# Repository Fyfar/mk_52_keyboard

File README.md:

# MK-52 Keyboard PCB Replacement

This repository contains a custom PCB design intended to replace the original, non-repairable keyboard board of the Soviet calculator **Elektronika MK-52**.

The board was designed and routed in **KiCad** as a personal project to restore my own calculator. I decided to publish the design files in case they are useful to other MK-52 owners facing similar keyboard failures.

---

## Background

The original keyboard assembly of the Elektronika MK-52 is difficult or impossible to repair once the membrane or contact layers degrade. Since original spare parts are no longer available, creating a replacement PCB becomes a practical restoration approach.

This project provides:

- A reverse-engineered keyboard PCB layout
- A modern, manufacturable replacement board
- KiCad project files for modification or adaptation

---

## Project Status

This is a **hobbyist restoration project** created for personal use.  
It is not an officially supported product and is not affiliated with the original manufacturer.

The design was tested on my own calculator, but hardware variations, component tolerances, and assembly differences may affect compatibility.

---

## Repository Contents

- KiCad project files (`.kicad_pro`)
- Schematic files
- PCB layout files
- Production-ready Gerber files

---

## Tools Used

- KiCad (PCB design and routing)

---

## Disclaimer

This project is provided **as-is**, without any warranties of any kind.

- It is an amateur project.
- There is no guarantee that it will work in your specific device.
- Manufacturing and installing this PCB requires electronics experience.
- Any attempt to disassemble or repair your calculator may result in permanent damage.
- You assume full responsibility for any damage caused during repair or modification.

If you are not confident in your repair skills, consider consulting an experienced electronics technician.

---

## Why This Exists

The Elektronika MK-52 is an iconic programmable calculator, and many units are still functional except for keyboard failures. This project exists to help preserve and restore these devices instead of letting them become unusable due to a single non-repairable component.

---

## License

CERN Open Hardware Licence Version 2 - Permissive

---

If this project helped you restore your MK-52, feel free to share your results or improvements.

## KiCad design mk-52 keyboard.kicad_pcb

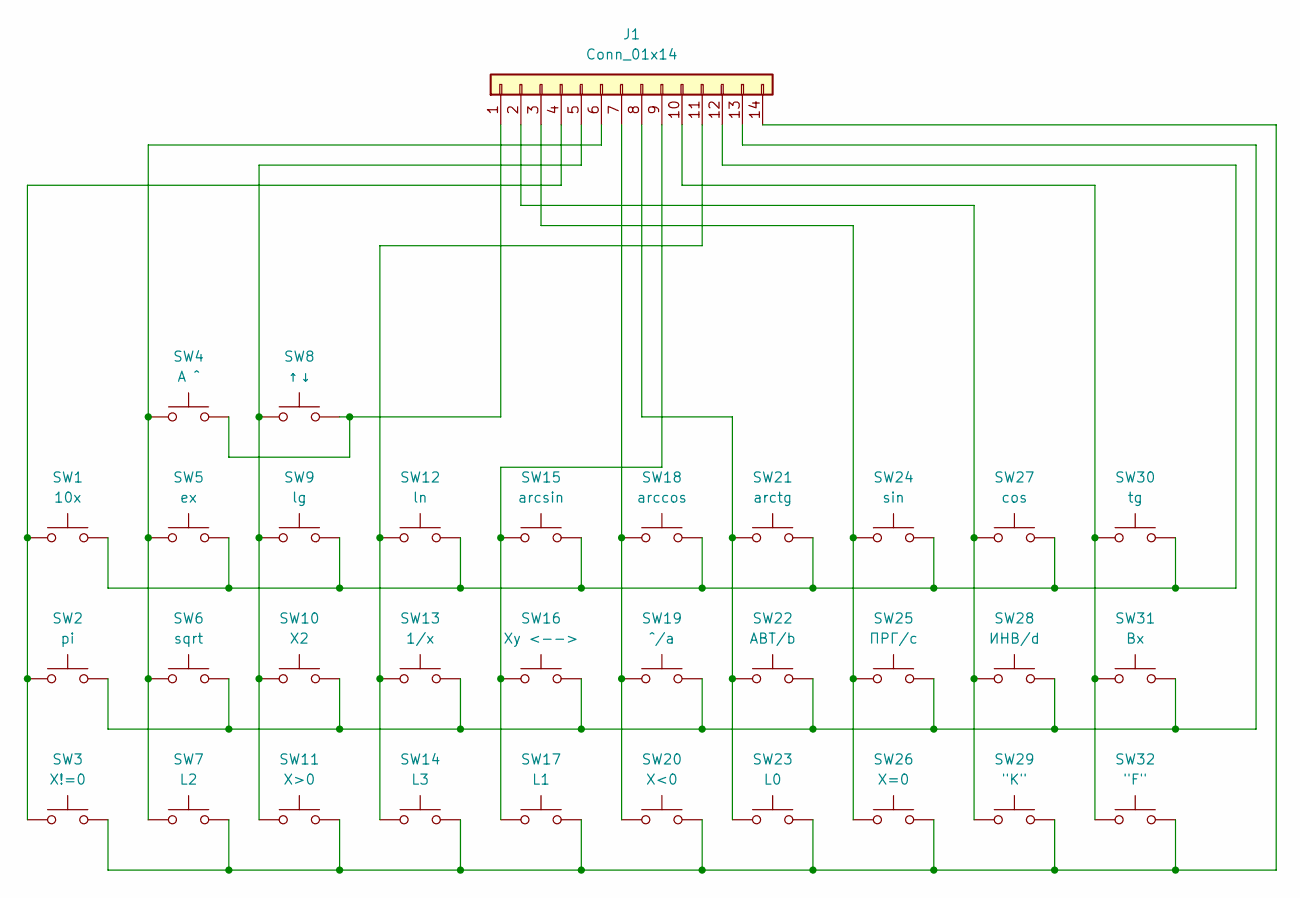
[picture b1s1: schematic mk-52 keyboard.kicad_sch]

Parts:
J1: Conn_01x14; FPC-14P-2.0mm
SW1: 10x; PUSH_TACT_4.8x4.8x0.8
SW2: pi; PUSH_TACT_4.8x4.8x0.8
SW3: X!=0; PUSH_TACT_4.8x4.8x0.8
SW4: A ^; PUSH_TACT_4.8x4.8x0.8
SW5: ex; PUSH_TACT_4.8x4.8x0.8
SW6: sqrt; PUSH_TACT_4.8x4.8x0.8
SW7: L2; PUSH_TACT_4.8x4.8x0.8
SW8: ↑↓; PUSH_TACT_4.8x4.8x0.8
SW9: lg; PUSH_TACT_4.8x4.8x0.8
SW10: X2; PUSH_TACT_4.8x4.8x0.8
SW11: X>0; PUSH_TACT_4.8x4.8x0.8
SW12: ln; PUSH_TACT_4.8x4.8x0.8
SW13: 1/x; PUSH_TACT_4.8x4.8x0.8
SW14: L3; PUSH_TACT_4.8x4.8x0.8
SW15: arcsin; PUSH_TACT_4.8x4.8x0.8
SW16: Xy <-->; PUSH_TACT_4.8x4.8x0.8
SW17: L1; PUSH_TACT_4.8x4.8x0.8
SW18: arccos; PUSH_TACT_4.8x4.8x0.8
SW19: ^/a; PUSH_TACT_4.8x4.8x0.8
SW20: X<0; PUSH_TACT_4.8x4.8x0.8
SW21: arctg; PUSH_TACT_4.8x4.8x0.8
SW22: АВТ/b; PUSH_TACT_4.8x4.8x0.8
SW23: L0; PUSH_TACT_4.8x4.8x0.8
SW24: sin; PUSH_TACT_4.8x4.8x0.8
SW25: ПРГ/c; PUSH_TACT_4.8x4.8x0.8
SW26: X=0; PUSH_TACT_4.8x4.8x0.8
SW27: cos; PUSH_TACT_4.8x4.8x0.8
SW28: ИНВ/d; PUSH_TACT_4.8x4.8x0.8
SW29: "K"; PUSH_TACT_4.8x4.8x0.8
SW30: tg; PUSH_TACT_4.8x4.8x0.8
SW31: Bx; PUSH_TACT_4.8x4.8x0.8
SW32: "F"; PUSH_TACT_4.8x4.8x0.8

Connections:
unnamed: J1.1, SW4.2, SW8.2
unnamed: J1.2, SW27.1, SW28.1, SW29.1
unnamed: J1.3, SW24.1, SW25.1, SW26.1
unnamed: J1.4, SW1.1, SW2.1, SW3.1
unnamed: J1.5, SW8.1, SW9.1, SW10.1, SW11.1
unnamed: J1.6, SW4.1, SW5.1, SW6.1, SW7.1
unnamed: J1.7, SW18.1, SW19.1, SW20.1
unnamed: J1.8, SW21.1, SW22.1, SW23.1
unnamed: J1.9, SW15.1, SW16.1, SW17.1
unnamed: J1.10, SW30.1, SW31.1, SW32.1
unnamed: J1.11, SW12.1, SW13.1, SW14.1
unnamed: J1.12, SW1.2, SW5.2, SW9.2, SW12.2, SW15.2, SW18.2, SW21.2, SW24.2, SW27.2, SW30.2
unnamed: J1.13, SW2.2, SW6.2, SW10.2, SW13.2, SW16.2, SW19.2, SW22.2, SW25.2, SW28.2, SW31.2
unnamed: J1.14, SW3.2, SW7.2, SW11.2, SW14.2, SW17.2, SW20.2, SW23.2, SW26.2, SW29.2, SW32.2

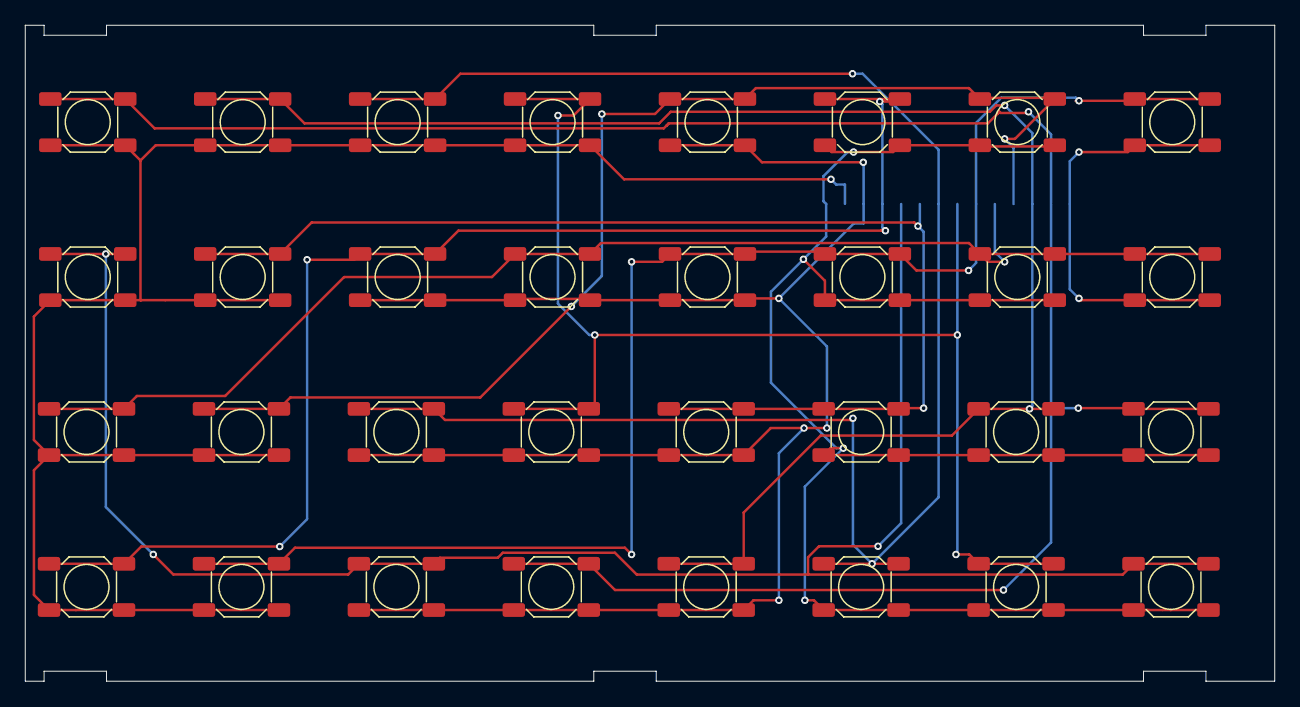
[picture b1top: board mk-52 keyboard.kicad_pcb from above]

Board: 2 copper layers, 100.0 x 52.5 mm, 33 parts (1 on the bottom side), 14 nets.

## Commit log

2026-03-03 Add CERN Open Hardware Licence Version 2 - Permissive
2026-03-03 Add KiCAD files
2026-03-03 Added Gerber files
2026-03-03 Revise README for MK-52 Keyboard PCB project
    Updated the README to provide detailed information about the MK-52 keyboard PCB replacement project, including background, project status, repository contents, tools used, disclaimer, and purpose.
